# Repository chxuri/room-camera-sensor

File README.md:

# Secoority Cam 
Do you have siblings who love "accidentally" wandering into your room and touching all your precious and definitely breakable stuff? Have you ever joked about your room needing more surveillance than your front door because of this very reason? Well it's time to stop joking, because the Secoority Cam is at your service! This is a motion sensor activated camera that sends footage to your phone every time it is activated. Obviously you don't want footage of you rotting in bed, so it also comes with a number pad that you can disable the camera with! You only have 10 seconds to input the right password though, so if you're too slow you'll get embarrasing footage on your computer of you failing to put in a 4 number passcode :P

## How it Works
The number pad (probably even more complex than the cam) is powered by a XIAO esp32, attatched to a PCB that is equipped with a motion sensor and a 0.91 inch OLED for those who can't remember more than two numbers at a time. A 10 second timer automatically starts the moment the motion sensor is activated, so the user has 10 seconds to input the correct password to disable the camera. When 10 seconds are up, the esp32 activates the camera and saves the footage. It stays on for as long as the motion sensor reads HIGH, and then has a 10 second cooldown so if the intruder happens to turn into a puddle, you'll still be able to see them for a little bit. 

## Why I Made This:
I have a little gremlin sibling who shows up randomly when I'm at school/sports practice. My parents refuse to do anything about it because it is "our home" so I was like ykw I'll just figure it out myself. (I also kind of had no other ideas and this seemed pretty cool lmao)

## Numpad
All 3D models are made by the one and only me! The top of this will be white and the base will be *hopefully* orange :D
(since i couldnt find a good 3d model for the camera, i made one myself! itll be connected by the ribbon cable it comes with, i just didnt know how to make that in fusion)

## PCB 

## Schematic 

### BOM
| Item                 | Price  | Quantity| Link  |
|----------------------|--------|---------|-------|
| OV5647 Camera        | $7.03  |    1    | <a href="https://www.aliexpress.us/item/3256802853835121.html">LINK</a> |
| 1N4148 Diodes        | $1.48  |    1    | <a href="https://www.aliexpress.us/item/2255799955957794.html">LINK</a> |
| Motion Sensor        | $1.58  |    1    | <a href="https://www.aliexpress.us/item/3256807881009549.html">LINK</a> |
| Micro SD (32G)       | $7.69  |    1    | <a href="https://shop.sandisk.com/products/memory-cards/microsd-cards/sandisk-ultra-uhs-i-microsd?sku=SDSQUNC-032G-AN6MA">LINK</a> |
| XIAO ESP32-S3 Sense  | $23.99 |    1    | <a href="https://a.co/d/cD5nkfC">LINK</a> |
| Cherry MX Switches   | $4.79  |    2    | <a href="https://a.co/d/3V39xDp">LINK</a> |
| OLED 0.91 Display    | $1.96  |    1    | <a href="https://www.aliexpress.us/item/3256805114690528.html">LINK</a> |
| 7 Pin Header         | $5.25  |    1    | <a href="https://a.co/d/dtQFQny">LINK</a> |
| Sensor Pin Header    | $1.49  |    1    | <a href="https://www.aliexpress.us/item/2251832777957007.html">LINK</a> |
| DSA Keycaps          | $3.29  |    1    | <a href="https://www.aliexpress.us/item/3256805819590269.html">LINK</a> |
| Numpad Screws        | $1.73  |    1    | <a href="https://www.aliexpress.us/item/3256806737710687.html">LINK</a> |
| Numpad Heatsets      | $2.16  |    1    | <a href="https://www.aliexpress.us/item/3256803396040989.html">LINK</a> |
| Micro USB Cable      | $1.71  |    1    | <a href="https://www.aliexpress.us/item/3256807553855991.html">LINK</a> |
| Micro SD Card Reader | $1.25  |    1    | <a href="https://www.aliexpress.us/item/2251832695439636.html">LINK</a> |
| PCB (pcbway)         | $5.00  |    1    | <a href="https://www.pcbway.com/">LINK</a> |
| Shipping (added)     | $15.31 |         |      |
| Sales Tax (added)    | $4.20  |         |      |
| Discounts (added)    | -$6.79 |         |      |
| Grand Total          | $87.91 |         |      |

*There are descriptions of each product in the BOM.csv file and also descriptions of where the shipping/tax costs are from...*

*I'll also need about $5 for shipping of my 3D printed cases from print legion :3*

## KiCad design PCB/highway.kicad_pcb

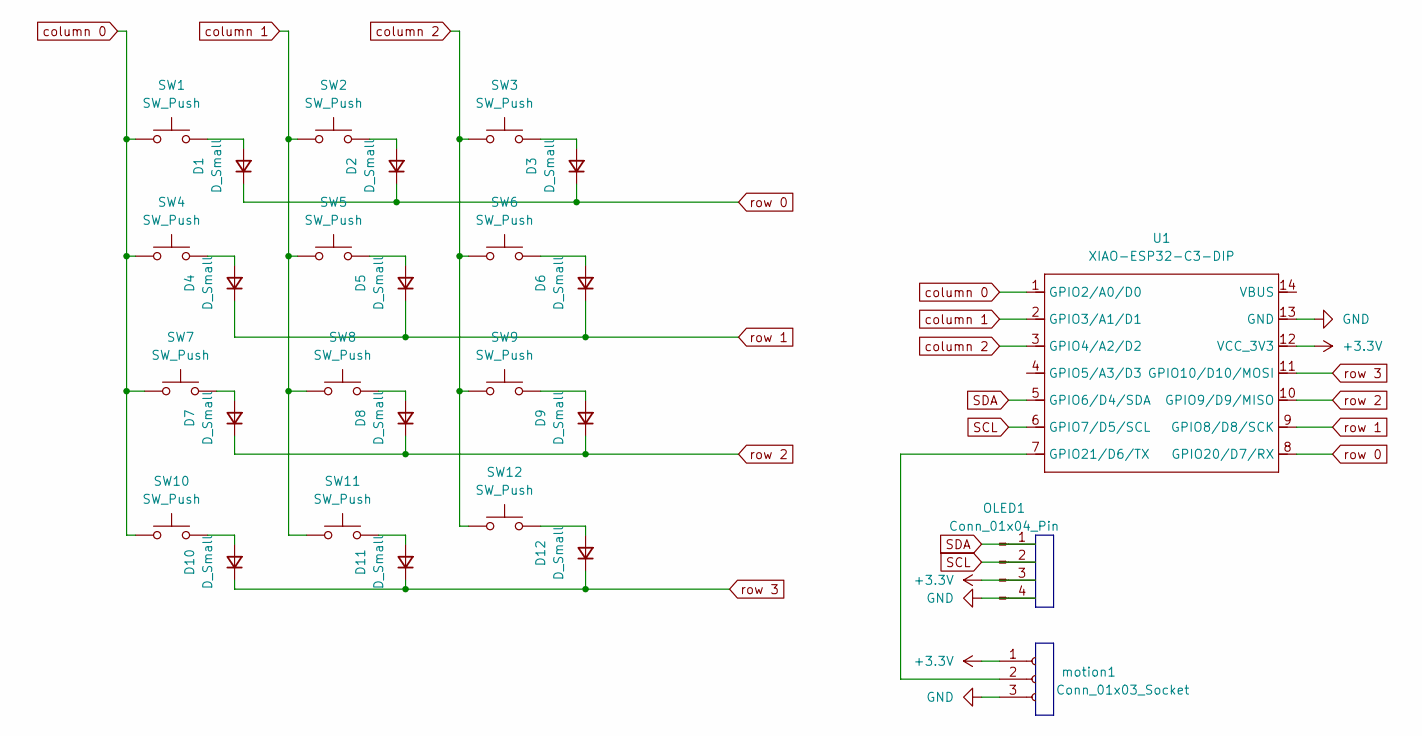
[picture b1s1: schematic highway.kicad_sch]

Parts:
D1, D2, D3, D4, D5, D6, D7, D8, D9, D10, D11, D12: D_Small; D_DO-35_SOD27_P3.81mm_Vertical_AnodeUp
OLED1: Conn_01x04_Pin; PinHeader_1x04_P2.54mm_Vertical
SW1, SW2, SW3, SW4, SW5, SW6, SW7, SW8, SW9, SW10, SW11, SW12: SW_Push; SW_Cherry_MX_1.00u_PCB
U1: XIAO-ESP32-C3-DIP; XIAO-ESP32C3-DIP
motion1: Conn_01x03_Socket; PinSocket_1x03_P2.54mm_Vertical

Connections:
+3.3V: OLED1.3, U1.12 (VCC_3V3), motion1.1
GND: OLED1.4, U1.13 (GND), motion1.3
unnamed: D1.2 (A), SW1.2
unnamed: D2.2 (A), SW2.2
unnamed: D3.2 (A), SW3.2
unnamed: D4.2 (A), SW4.2
unnamed: D5.2 (A), SW5.2
unnamed: D6.2 (A), SW6.2
unnamed: D7.2 (A), SW7.2
unnamed: D8.2 (A), SW8.2
unnamed: D9.2 (A), SW9.2
unnamed: D10.2 (A), SW10.2
unnamed: D11.2 (A), SW11.2
unnamed: D12.2 (A), SW12.2
unnamed: U1.7 (GPIO21/D6/TX), motion1.2
SCL: OLED1.2, U1.6 (GPIO7/D5/SCL)
SDA: OLED1.1, U1.5 (GPIO6/D4/SDA)
column 0: SW1.1, SW4.1, SW7.1, SW10.1, U1.1 (GPIO2/A0/D0)
column 1: SW2.1, SW5.1, SW8.1, SW11.1, U1.2 (GPIO3/A1/D1)
column 2: SW3.1, SW6.1, SW9.1, SW12.1, U1.3 (GPIO4/A2/D2)
row 0: D1.1 (K), D2.1 (K), D3.1 (K), U1.8 (GPIO20/D7/RX)
row 1: D4.1 (K), D5.1 (K), D6.1 (K), U1.9 (GPIO8/D8/SCK)
row 2: D7.1 (K), D8.1 (K), D9.1 (K), U1.10 (GPIO9/D9/MISO)
row 3: D10.1 (K), D11.1 (K), D12.1 (K), U1.11 (GPIO10/D10/MOSI)

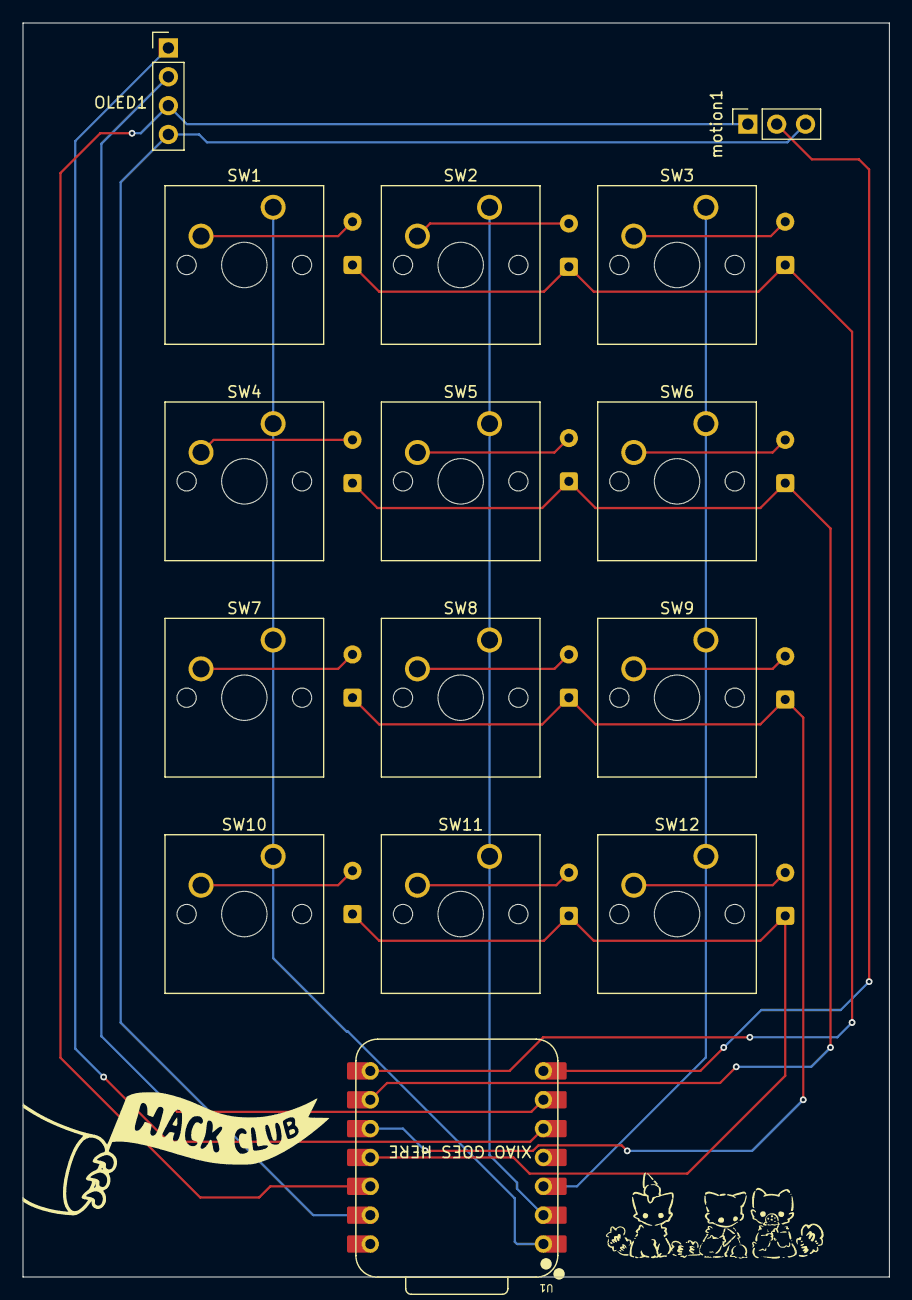
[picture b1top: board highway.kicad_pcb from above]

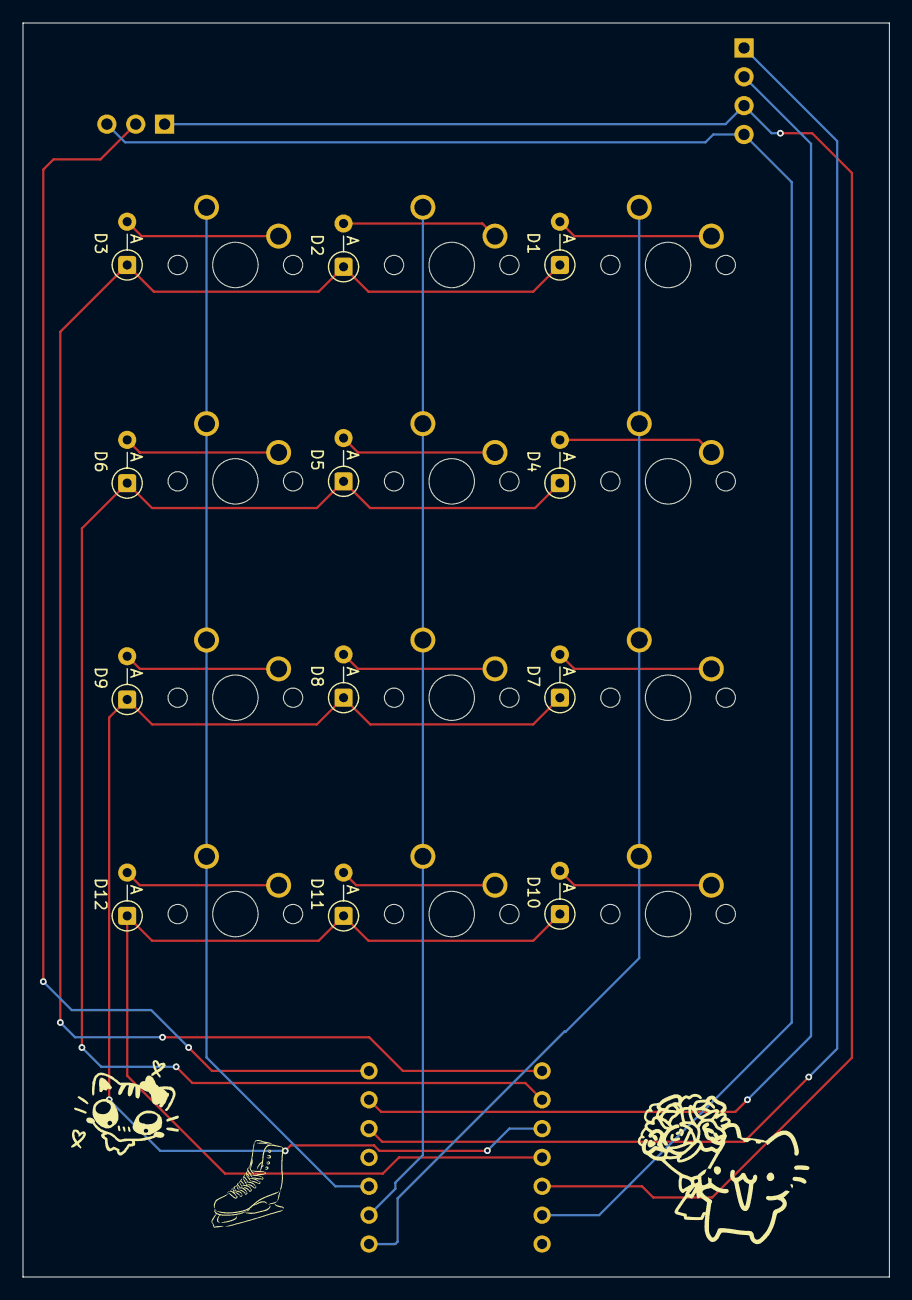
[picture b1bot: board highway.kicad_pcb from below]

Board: 2 copper layers, 76.3 x 110.4 mm, 27 parts (12 on the bottom side), 24 nets.

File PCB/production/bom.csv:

Designator,Footprint,Quantity,Value,LCSC Part #
"D1, D10, D11, D12, D2, D3, D4, D5, D6, D7, D8, D9",D_DO-35_SOD27_P3.81mm_Vertical_AnodeUp,12,D_Small,
MOTION1,PinSocket_1x03_P2.54mm_Vertical,1,Conn_01x03_Socket,
OLED1,PinHeader_1x04_P2.54mm_Vertical,1,Conn_01x04_Pin,
"SW1, SW10, SW11, SW12, SW2, SW3, SW4, SW5, SW6, SW7, SW8, SW9",SW_Cherry_MX_1.00u_PCB,12,SW_Push,
U1,XIAO-ESP32C3-DIP,1,XIAO-ESP32-C3-DIP,

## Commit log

2025-07-02 created journal
2025-07-06 journal progress update
2025-07-06 journal progress update fix
2025-07-06 fixed journal formatting
2025-07-06 more format fixing
2025-07-07 fixed image format
2025-07-14 fixing image sizing
2025-07-14 final image fixing update
2025-07-19 Journal progress update (fusion is so ass im tired of working w ts jdhiwhdfiwglfwhebfek)
2025-07-25 fixed lil issue
2025-07-27 uploading le bomb
2025-07-27 fixed le bomb
2025-07-27 updated le bomb's name
2025-07-27 add pcb filez
2025-07-27 rename filez
2025-07-27 upload cad :3
2025-07-28 working on firmware
2025-07-28 Rename espMicrocontroller.ino to firmware.ino
2025-07-28 FINISHED FIRMWARE LES GOO
2025-07-28 fixed a lil oopsie
2025-07-28 added images YAY
2025-07-28 fixed titles lol
2025-07-28 Rename numpad_top.png to numpad_assembly.png
2025-07-28 Rename numpads_top.png to numpad_top.png
2025-07-28 ew go away
2025-07-28 FINAL JOURNAL UPDATE YIPEE
2025-07-28 BRO GO AWAY
2025-07-28 goobye
2025-07-28 fixed lil thingy
2025-07-28 huhhh
2025-07-28 bruh ts aint working
2025-07-28 Create LICENSE
2025-07-28 license done (lice)
2025-07-30 uploading wiring diagram for raspi :P
2025-07-30 Rename IMG_0614.jpg to wiring_diagram.jpg
2025-07-31 Add .DS_Store to .gitignore
2025-07-31 Stop tracking .DS_Store
2025-08-01 resubmission changes
2025-08-01 uploading pcb source filez
